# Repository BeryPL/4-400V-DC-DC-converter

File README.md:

This is a simple PCB design for a 4 to 400 V DC/DC converter, based on a LT8304 IC.
Made as a high voltage power supply for a Geiger-Muller lamp in my dosimeter project.

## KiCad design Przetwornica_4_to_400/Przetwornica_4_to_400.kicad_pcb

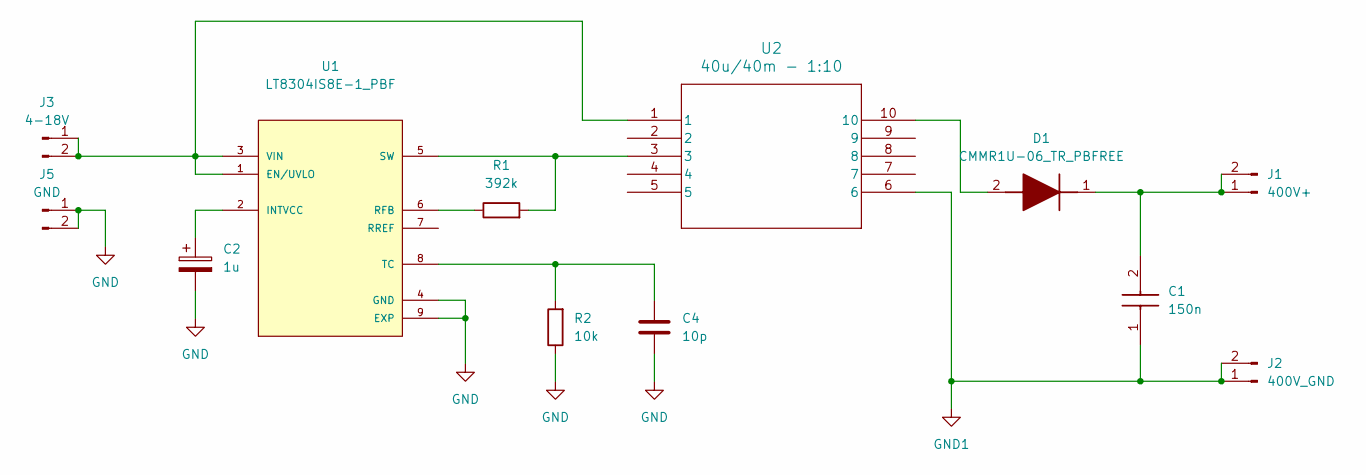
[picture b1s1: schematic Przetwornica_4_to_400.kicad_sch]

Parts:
C1: 150n; 890303325008CS; Mouser Part Number 710-890303325008CS
C2: 1u; CP_Radial_D4.0mm_P1.50mm
C4: 10p; C_0805_2012Metric
D1: CMMR1U-06_TR_PBFREE; SODFL3818X108N; Mouser Part Number 610-CMMR1U-06
J1: 400V+; PinHeader_1x02_P2.54mm_Vertical
J2: 400V_GND; PinHeader_1x02_P2.54mm_Vertical
J3: 4-18V; PinHeader_1x02_P2.54mm_Vertical
J5: GND; PinHeader_1x02_P2.54mm_Vertical
R1: 392k; R_0805_2012Metric
R2: 10k; R_0805_2012Metric
U1: LT8304IS8E-1_PBF; SOIC127P599X175-9N; PARTREV LT0217_REV_A
U2: 40u/40m - 1:10; SMT_24-T087_SUM

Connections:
GND: C2.2, C4.2, J5.1, J5.2, R2.1, U1.4 (GND), U1.9 (EXP)
GND1: C1.1, J2.1, J2.2, U2.6
unnamed: D1.2 (A), U2.10
unnamed: C1.2, D1.1 (K), J1.1, J1.2
unnamed: J3.1, J3.2, U1.1 (EN/UVLO), U1.3 (VIN), U2.1
unnamed: C2.1, U1.2 (INTVCC)
unnamed: R1.1, U1.6 (RFB)
unnamed: R1.2, U1.5 (SW), U2.3
unnamed: C4.1, R2.2, U1.8 (TC)

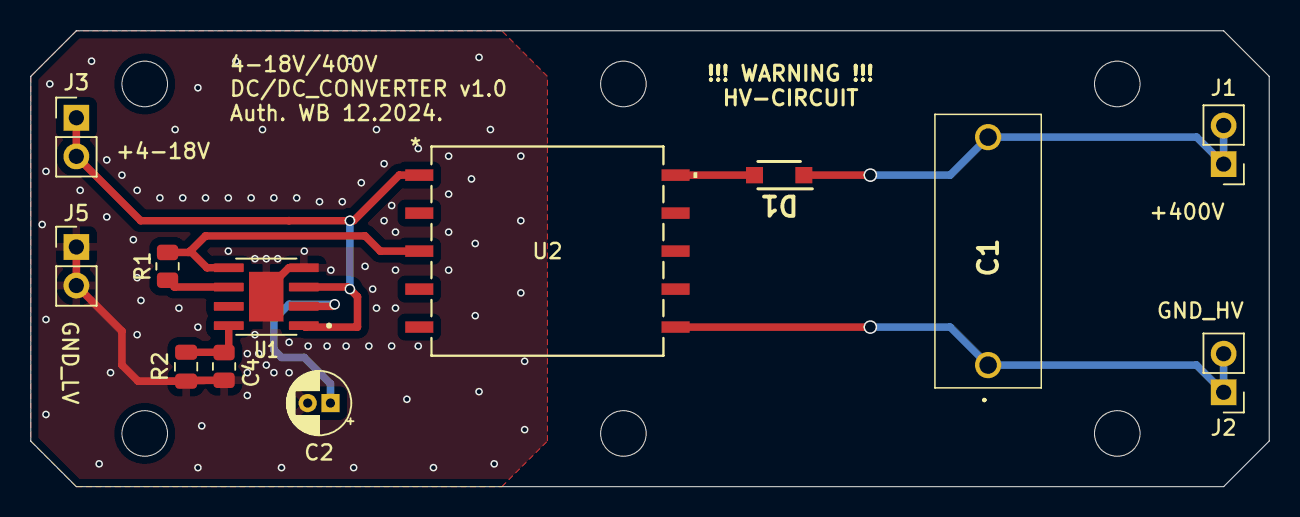
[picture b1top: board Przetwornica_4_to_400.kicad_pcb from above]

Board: 2 copper layers, 81.5 x 30.0 mm, 12 parts (0 on the bottom side), 9 nets.

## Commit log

2025-01-16 added README
